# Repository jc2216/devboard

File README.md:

# devboard

this is a devboard i worked really hard on it it's basically raspberry pi pico copy except it doesn't support an alternative battery supply which is depressing. i also added an led because it's fun.

the routing was really painful do not recomment

more painful things

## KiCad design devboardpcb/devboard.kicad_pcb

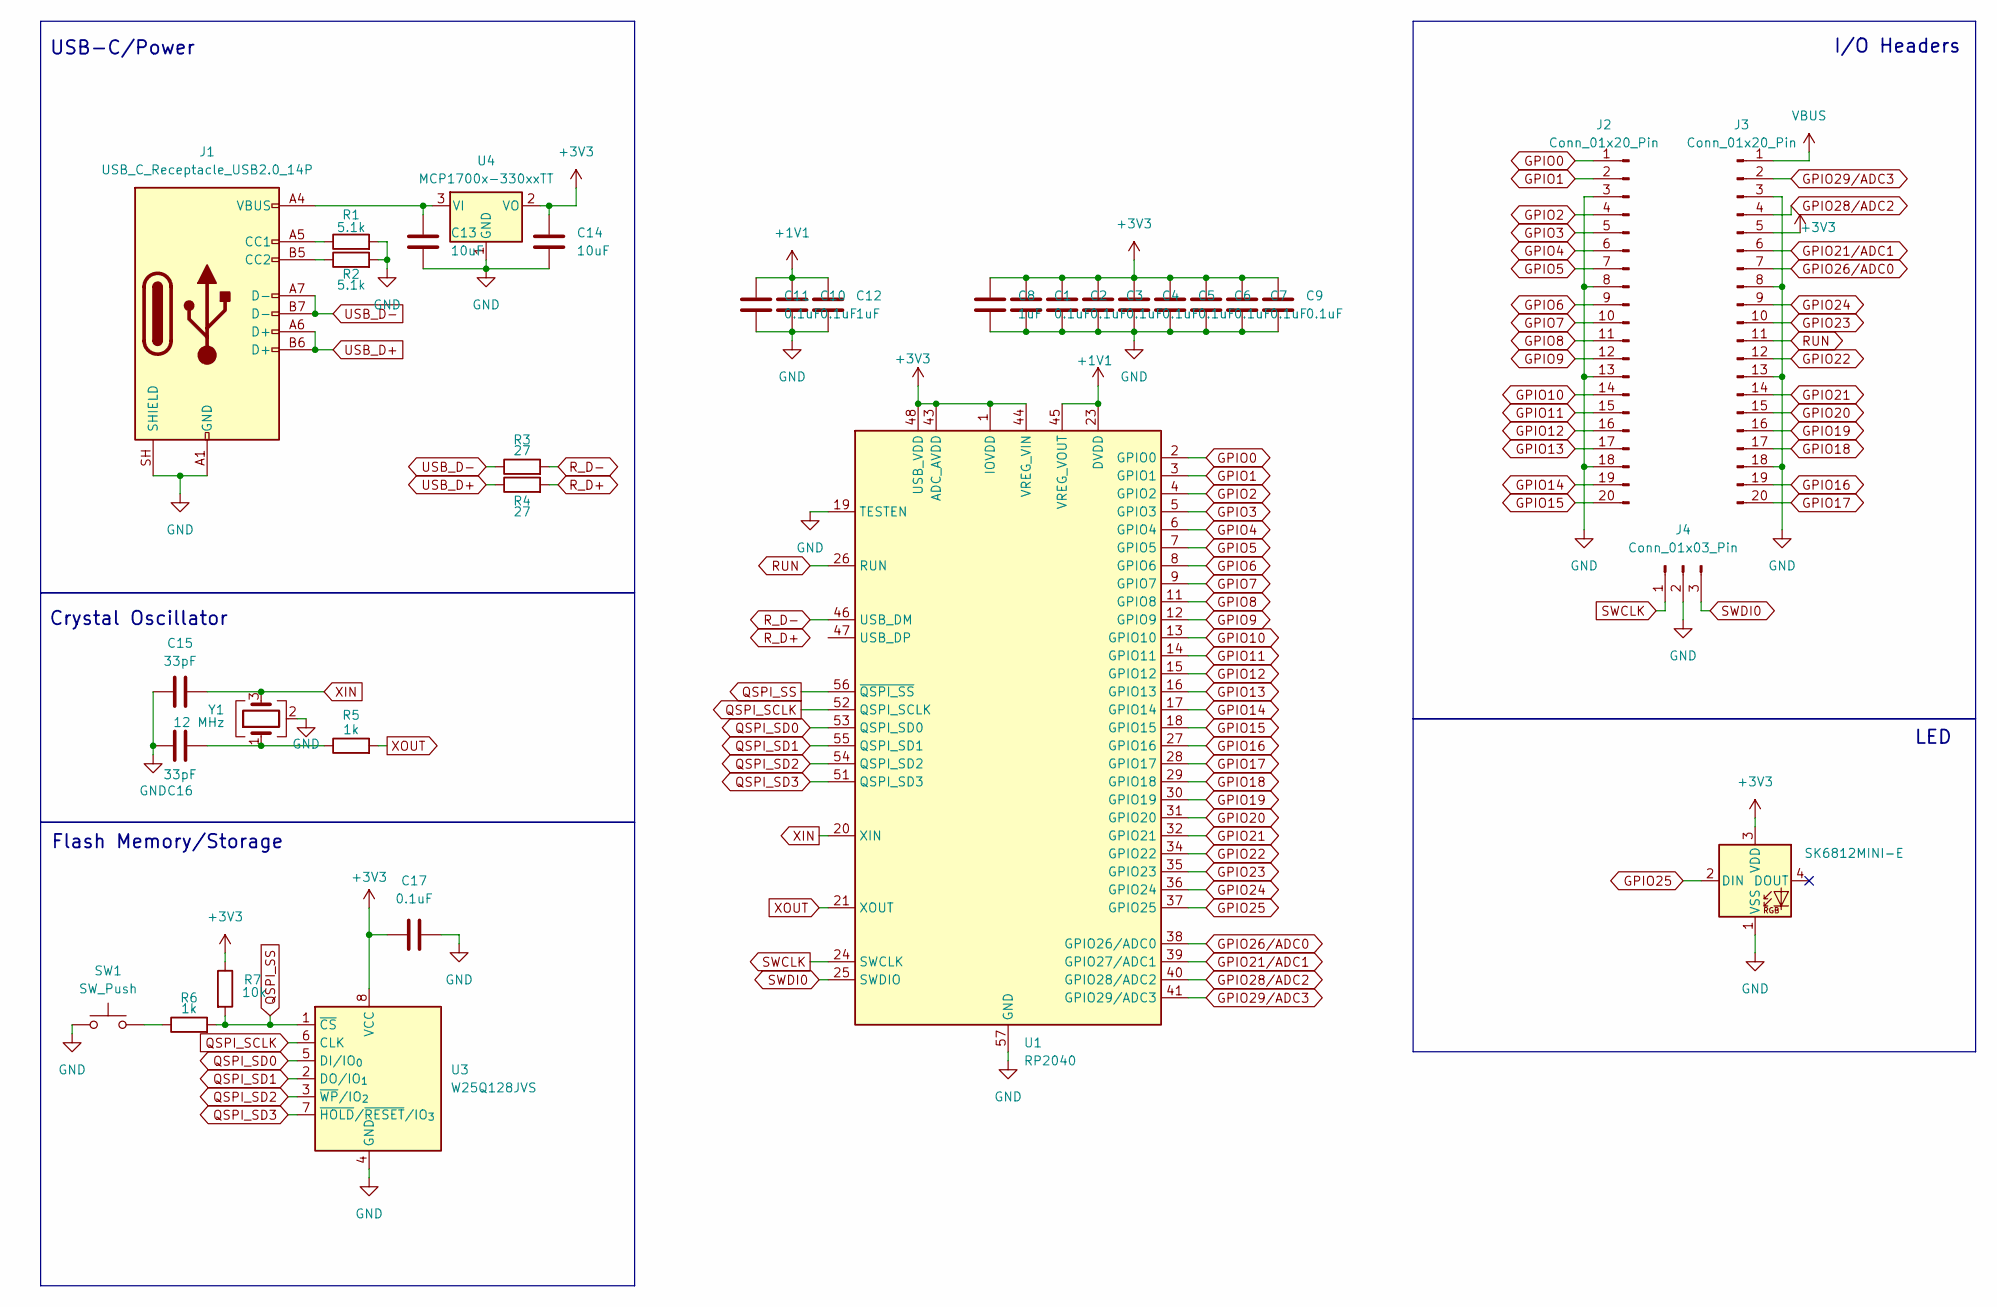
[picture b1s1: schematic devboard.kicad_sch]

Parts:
C1, C2, C3, C4, C5, C6, C7, C9, C10, C11, C17: 0.1uF; C_0402_1005Metric
C8, C12: 1uF; C_0402_1005Metric
C13, C14: 10uF; C_0603_1608Metric
C15, C16: 33pF; C_0402_1005Metric
D2: SK6812MINI-E; LED_SK6812MINI-E_3.2x2.8mm_P1.5mm_ReverseMount
J1: USB_C_Receptacle_USB2.0_14P; USB_C_Receptacle_HRO_TYPE-C-31-M-12
J2, J3: Conn_01x20_Pin; PinHeader_1x20_P2.54mm_Vertical
J4: Conn_01x03_Pin; PinHeader_1x03_P2.54mm_Vertical
R1, R2: 5.1k; R_0402_1005Metric
R3, R4: 27; R_0402_1005Metric
R5, R6: 1k; R_0402_1005Metric
R7: 10k; R_0402_1005Metric
SW1: SW_Push; SW_TS-1088-AR02016
U1: RP2040; QFN-56-1EP_7x7mm_P0.4mm_EP3.2x3.2mm
U3: W25Q128JVS; SOIC-8_5.3x5.3mm_P1.27mm
U4: MCP1700x-330xxTT; SOT-23
Y1: 12 MHz; Crystal_SMD_3225-4Pin_3.2x2.5mm

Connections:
+1V1: C10.1, C11.1, C12.1, U1.23 (DVDD), U1.45 (VREG_VOUT), U1.50 (DVDD)
+3V3: C1.1, C2.1, C3.1, C4.1, C5.1, C6.1, C7.1, C8.1, C9.1, C14.1, C17.1, D2.3 (VDD), J3.5, R7.1, U1.1 (IOVDD), U1.10 (IOVDD), U1.22 (IOVDD), U1.33 (IOVDD), U1.42 (IOVDD), U1.43 (ADC_AVDD), U1.44 (VREG_VIN), U1.48 (USB_VDD), U1.49 (IOVDD), U3.8 (VCC), U4.2 (VO)
GND: C1.2, C2.2, C3.2, C4.2, C5.2, C6.2, C7.2, C8.2, C9.2, C10.2, C11.2, C12.2, C13.2, C14.2, C15.1, C16.1, C17.2, D2.1 (VSS), J1.A1 (GND), J1.A12 (GND), J1.B1 (GND), J1.B12 (GND), J1.SH (SHIELD), J2.3, J2.8, J2.13, J2.18, J3.3, J3.8, J3.13, J3.18, J4.2, R1.2, R2.2, SW1.1, U1.19 (TESTEN), U1.57 (GND), U3.4 (GND), U4.1 (GND), Y1.2 (G), Y1.4 (G)
GPIO0: J2.1, U1.2 (GPIO0)
GPIO1: J2.2, U1.3 (GPIO1)
GPIO2: J2.4, U1.4 (GPIO2)
GPIO3: J2.5, U1.5 (GPIO3)
GPIO4: J2.6, U1.6 (GPIO4)
GPIO5: J2.7, U1.7 (GPIO5)
GPIO6: J2.9, U1.8 (GPIO6)
GPIO7: J2.10, U1.9 (GPIO7)
GPIO8: J2.11, U1.11 (GPIO8)
GPIO9: J2.12, U1.12 (GPIO9)
GPIO10: J2.14, U1.13 (GPIO10)
GPIO11: J2.15, U1.14 (GPIO11)
GPIO12: J2.16, U1.15 (GPIO12)
GPIO13: J2.17, U1.16 (GPIO13)
GPIO14: J2.19, U1.17 (GPIO14)
GPIO15: J2.20, U1.18 (GPIO15)
GPIO16: J3.19, U1.27 (GPIO16)
GPIO17: J3.20, U1.28 (GPIO17)
GPIO18: J3.17, U1.29 (GPIO18)
GPIO19: J3.16, U1.30 (GPIO19)
GPIO20: J3.15, U1.31 (GPIO20)
GPIO21: J3.14, U1.32 (GPIO21)
GPIO21/ADC1: J3.6, U1.39 (GPIO27/ADC1)
GPIO22: J3.12, U1.34 (GPIO22)
GPIO23: J3.10, U1.35 (GPIO23)
GPIO24: J3.9, U1.36 (GPIO24)
GPIO25: D2.2 (DIN), U1.37 (GPIO25)
GPIO26/ADC0: J3.7, U1.38 (GPIO26/ADC0)
GPIO28/ADC2: J3.4, U1.40 (GPIO28/ADC2)
GPIO29/ADC3: J3.2, U1.41 (GPIO29/ADC3)
unnamed: C16.2, R5.1, Y1.1
unnamed: J1.A5 (CC1), R1.1
unnamed: J1.B5 (CC2), R2.1
unnamed: R6.1, SW1.2
unnamed: C13.1, J1.A4 (VBUS), J1.A9 (VBUS), J1.B4 (VBUS), J1.B9 (VBUS), U4.3 (VI)
QSPI_SCLK: U1.52 (QSPI_SCLK), U3.6 (CLK)
QSPI_SD0: U1.53 (QSPI_SD0), U3.5 (DI/IO_{0})
QSPI_SD1: U1.55 (QSPI_SD1), U3.2 (DO/IO_{1})
QSPI_SD2: U1.54 (QSPI_SD2), U3.3 (~WP/IO_{2})
QSPI_SD3: U1.51 (QSPI_SD3), U3.7 (~HOLD/~RESET/IO_{3})
QSPI_SS: R6.2, R7.2, U1.56 (~QSPI_SS), U3.1 (~CS)
RUN: J3.11, U1.26 (RUN)
R_D+: R4.2, U1.47 (USB_DP)
R_D-: R3.2, U1.46 (USB_DM)
SWCLK: J4.1, U1.24 (SWCLK)
SWDI0: J4.3, U1.25 (SWDIO)
USB_D+: J1.A6 (D+), J1.B6 (D+), R4.1
USB_D-: J1.A7 (D-), J1.B7 (D-), R3.1
VBUS: J3.1
XIN: C15.2, U1.20 (XIN), Y1.3
XOUT: R5.2, U1.21 (XOUT)

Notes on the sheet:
LED
USB-C/Power
I/O Headers
Crystal Oscillator
Flash Memory/Storage

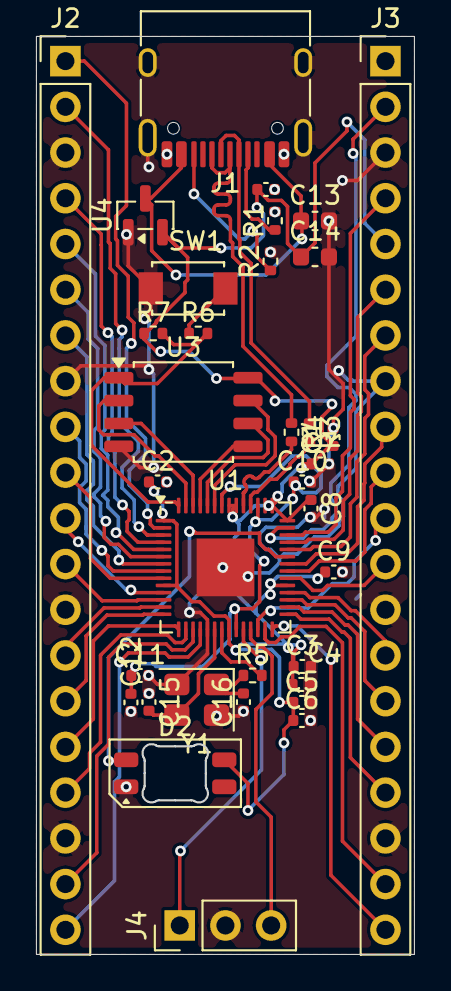
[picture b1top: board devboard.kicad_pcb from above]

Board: 2 copper layers, 21.0 x 51.0 mm, 34 parts (0 on the bottom side), 53 nets.

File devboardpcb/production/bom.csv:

Designator,Footprint,Quantity,Value,LCSC Part #
"C1, C10, C11, C17, C2, C3, C4, C5, C6, C7, C9",0402,11,0.1uF,
"C12, C8",0402,2,1uF,
"C13, C14",0603,2,10uF,
"C15, C16",0402,2,33pF,
D2,LED_SK6812MINI-E_3.2x2.8mm_P1.5mm_ReverseMount,1,SK6812MINI-E,
J1,USB_C_Receptacle_HRO_TYPE-C-31-M-12,1,USB_C_Receptacle_USB2.0_14P,
"J2, J3",PinHeader_1x20_P2.54mm_Vertical,2,Conn_01x20_Pin,
J4,PinHeader_1x03_P2.54mm_Vertical,1,Conn_01x03_Pin,
"R1, R2",0402,2,5.1k,
"R3, R4",0402,2,27,
"R5, R6",0402,2,1k,
R7,0402,1,10k,
SW1,SW_TS-1088-AR02016,1,SW_Push,
U1,QFN-56-1EP_7x7mm_P0.4mm_EP3.2x3.2mm,1,RP2040,
U3,SOIC-8_5.3x5.3mm_P1.27mm,1,W25Q128JVS,
U4,SOT-23,1,MCP1700x-330xxTT,
Y1,Crystal_SMD_3225-4Pin_3.2x2.5mm,1,12 MHz,
